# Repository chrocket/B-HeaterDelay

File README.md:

# B-HeaterDelay

B+ Heater Delay

SMD version of Pete Millett B++ heater delay (only delay portion) http://www.pmillett.com/mec\_power\_supply\_delay.html

The "main" branch has a one relay version.  Use 6/28/25 production files

Branch "dual" has two relays.  Use B_Delay_20260203_rev5d.zip production files.

I'm using KiCad 9.0.0

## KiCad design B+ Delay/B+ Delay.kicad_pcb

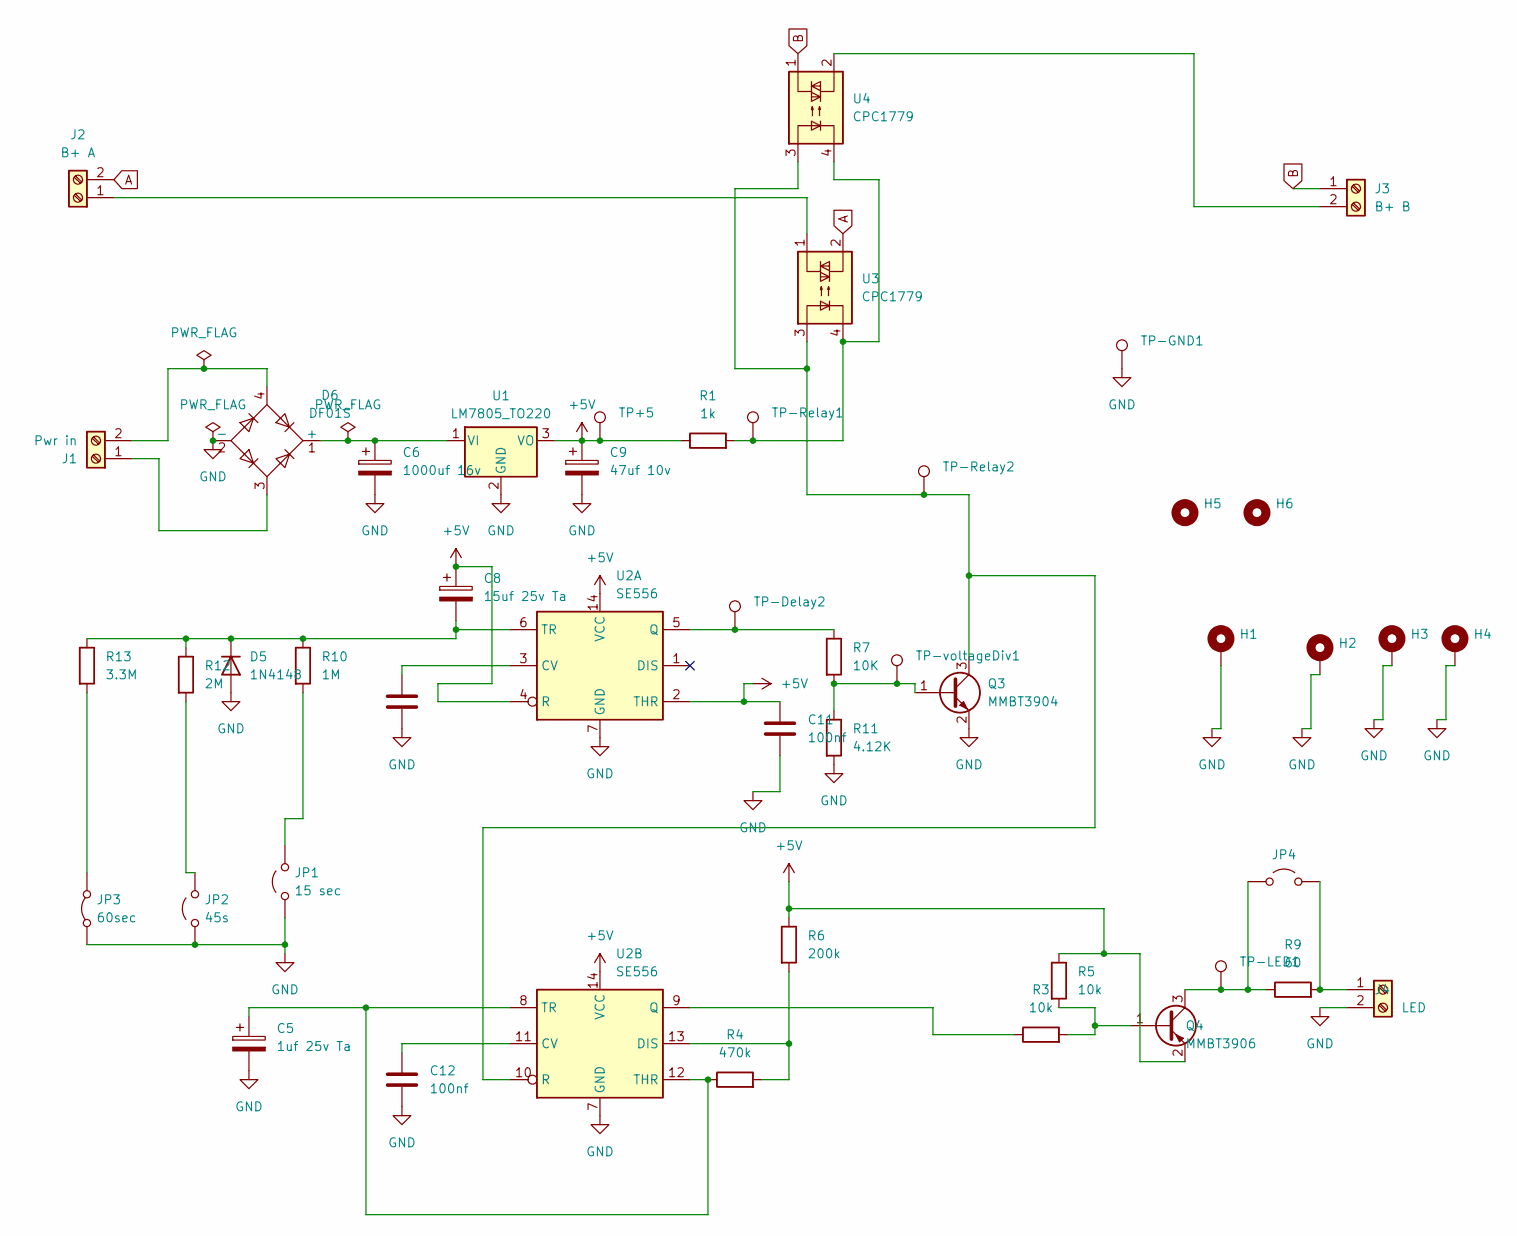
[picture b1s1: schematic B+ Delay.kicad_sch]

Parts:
C5: 1uf 25v Ta; C_0805_2012Metric_Pad1.18x1.45mm_HandSolder; Mouser 74-TMCP1E105KTRF
C6: 1000uf 16v; CP_Elec_10x7.7; Mouser 647-UCL1C102MNL1GS
C8: 15uf 25v Ta; C_1210_3225Metric_Pad1.33x2.70mm_HandSolder; Mouser 581-TPSB156K016R0800
C9: 47uf 10v; CP_Elec_10x7.7; Mouser 647-PCF1E470MCL1GS
C10, C11, C12: 100nf; C_0805_2012Metric; LCSC C49678
D5: 1N4148; D_SOD-123; LCSC C2128
D6: DF01S; Diode_Bridge_OnSemi_SDIP-4L; Mouser 621-DF01ST
H1, H2, H3, H4: MountingHole_4.3mm_M4_DIN965_Pad_TopBottom
H5: MountingHole; MountingHole_3.2mm_M3_Pad_TopBottom
H6: MountingHole; MountingHole_3.2mm_M3_ISO14580_Pad_TopBottom
J1: Pwr in; TerminalBlock_Phoenix_PT-1,5-2-3.5-H_1x02_P3.50mm_Horizontal
J2: B+ A; TerminalBlock_CUI_TB007-508-02_1x02_P5.08mm_Horizontal
J3: B+ B; TerminalBlock_CUI_TB007-508-02_1x02_P5.08mm_Horizontal
J4: LED; TerminalBlock_Phoenix_PT-1,5-2-3.5-H_1x02_P3.50mm_Horizontal
JP1: 15 sec; SolderJumper-2_P1.3mm_Open_RoundedPad1.0x1.5mm
JP2: 45s; SolderJumper-2_P1.3mm_Open_RoundedPad1.0x1.5mm
JP3: 60sec; SolderJumper-2_P1.3mm_Bridged_Pad1.0x1.5mm
JP4: Jumper_2_Open; SolderJumper-2_P1.3mm_Open_RoundedPad1.0x1.5mm
Q3: MMBT3904; SOT-23; LCSC C20526
Q4: MMBT3906; SOT-23; LCSC C5300004
R1: 1k; R_0805_2012Metric_Pad1.20x1.40mm_HandSolder; LCSC C17513
R3, R5: 10k; R_0805_2012Metric_Pad1.20x1.40mm_HandSolder; LCSC C17414
R4: 470k; R_0805_2012Metric_Pad1.20x1.40mm_HandSolder; LCSC C17709
R6: 200k; R_0805_2012Metric_Pad1.20x1.40mm_HandSolder; LCSC C17539
R7: 10K; R_0805_2012Metric_Pad1.20x1.40mm_HandSolder; LCSC C17414
R9: 60; R_0805_2012Metric_Pad1.20x1.40mm_HandSolder; LCSC C17757
R10: 1M; R_0805_2012Metric_Pad1.20x1.40mm_HandSolder; LCSC C17514
R11: 4.12K; R_0805_2012Metric_Pad1.20x1.40mm_HandSolder; LCSC C17667
R12: 2M; R_0805_2012Metric_Pad1.20x1.40mm_HandSolder; LCSC C17514
R13: 3.3M; R_0805_2012Metric_Pad1.20x1.40mm_HandSolder; LCSC C17514
TP+5: TestPoint_Keystone_5019_Miniature
TP-Delay2: TestPoint_Keystone_5019_Miniature
TP-GND1: TestPoint_Keystone_5019_Miniature
TP-LED1: TestPoint_Keystone_5019_Miniature
TP-Relay1, TP-Relay2: TestPoint_Keystone_5019_Miniature
TP-voltageDiv1: TestPoint_Keystone_5019_Miniature
U1: LM7805_TO220; TO-252-2; LCSC C110908
U2: SE556; SOIC-14_3.9x8.7mm_P1.27mm; LCSC C7427
U3, U4: CPC1779; CPC1779J

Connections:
+5V: C8.1, C9.1, C11.1, Q4.2 (E), R1.1, R5.1, R6.1, TP+5.1, U1.3 (VO), U2.2 (THR), U2.4 (R), U2.14 (VCC)
A: J2.2, U3.2
B: J3.1, U4.1
GND: C5.2, C6.2, C9.2, C10.2, C11.2, C12.2, D5.2 (A), D6.2 (-), H1.1, H2.1, H3.1, H4.1, J4.2, JP1.1 (A), JP2.1 (A), JP3.1 (A), Q3.2 (E), R11.2, TP-GND1.1, U1.2 (GND), U2.7 (GND)
unnamed: C8.2, D5.1 (K), R10.1, R12.1, R13.1, U2.6 (TR)
unnamed: C6.1, D6.1 (+), U1.1 (VI)
unnamed: D6.3, J1.1
unnamed: D6.4, J1.2
unnamed: J2.1, U3.1
unnamed: J3.2, U4.2
unnamed: J4.1, JP4.2 (B), R9.2
unnamed: JP1.2 (B), R10.2
unnamed: JP2.2 (B), R12.2
unnamed: JP3.2 (B), R13.2
unnamed: JP4.1 (A), Q4.3 (C), R9.1, TP-LED1.1
unnamed: Q3.1 (B), R7.2, R11.1, TP-voltageDiv1.1
unnamed: Q3.3 (C), TP-Relay2.1, U2.10 (R), U3.3, U4.3
unnamed: Q4.1 (B), R3.2, R5.2
unnamed: R1.2, TP-Relay1.1, U3.4, U4.4
unnamed: C10.1, U2.3 (CV)
unnamed: R7.1, TP-Delay2.1, U2.5 (Q)
unnamed: C12.1, U2.11 (CV)
unnamed: R4.2, R6.2, U2.13 (DIS)
unnamed: R3.1, U2.9 (Q)
unnamed: C5.1, R4.1, U2.8 (TR), U2.12 (THR)

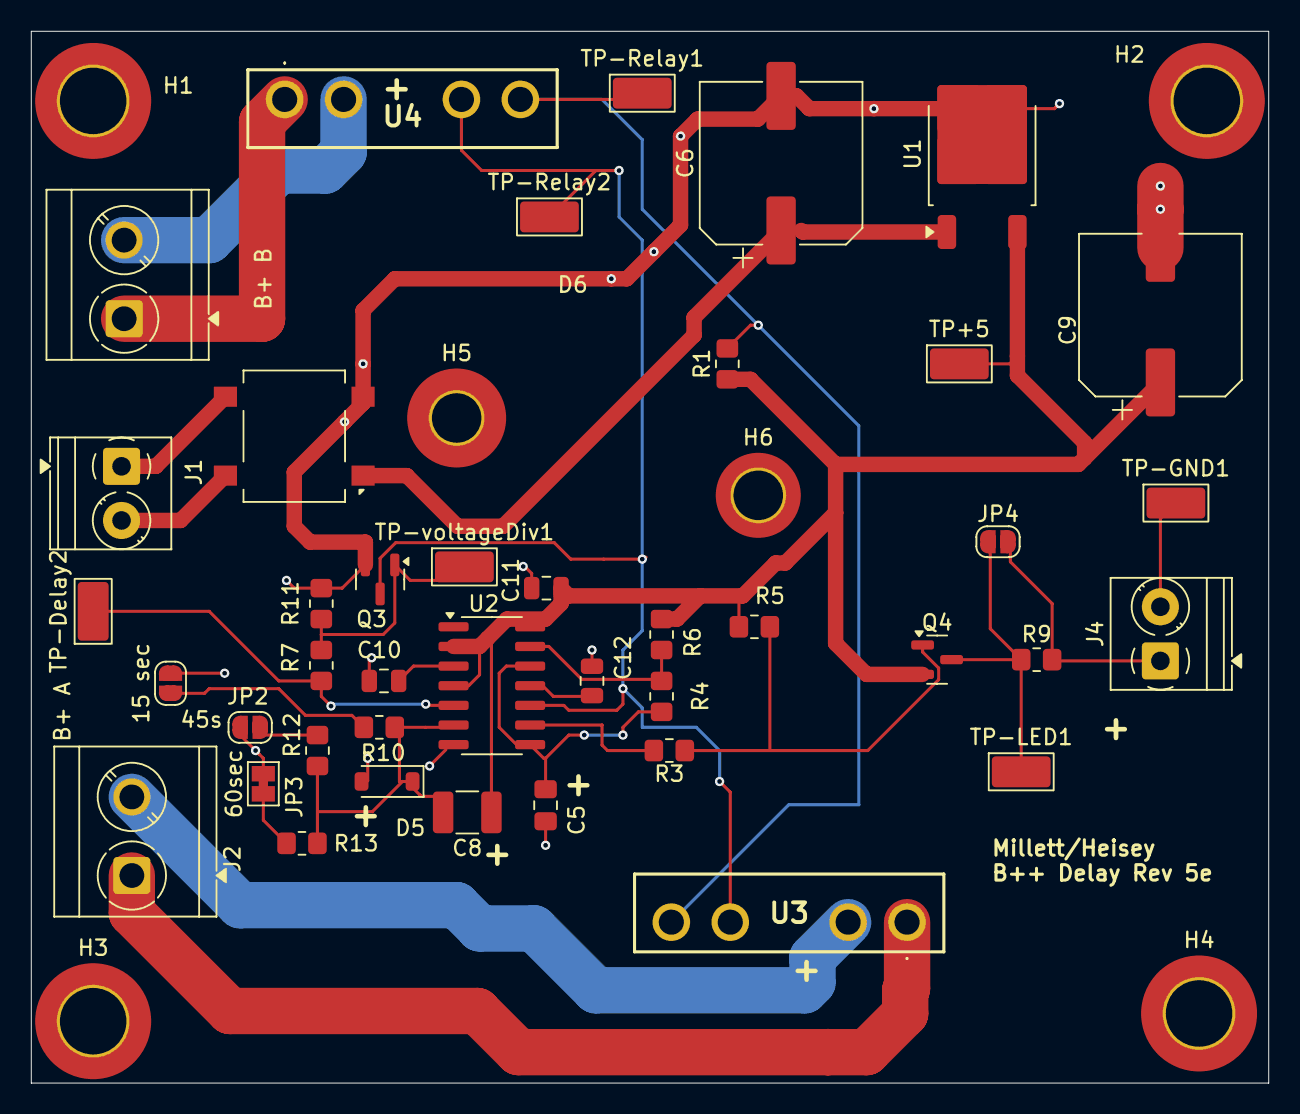
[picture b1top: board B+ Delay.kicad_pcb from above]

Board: 2 copper layers, 80.0 x 68.0 mm, 47 parts (0 on the bottom side), 25 nets.

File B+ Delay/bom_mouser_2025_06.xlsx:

Designator | Footprint | Quantity used | Quantity Order | Value | Mouser Part Number
C10, C11, C12 | 805 | 3 |  | 100nf | 0805B104K250CT
C5 | 805 | 1 |  | 1uf 25v Ta | TMCP1E105KTRF
C6 | CP_Elec_10x7.7 | 1 |  | 1000uf 16v | 667-EEE-FK1A102GP
C8 | 1210 | 1 |  | 15uf 25v Ta | TPSB156K016R0800
C9 | CP_Elec_10x7.7 | 1 |  | 47uf 10v | 667-EEE-FK1K470P
D5 | 805 | 1 |  | 1N4148 | 241-1N4148W_R1_00001
D6 | Diode_Bridge_OnSemi_SDIP-4L | 1 |  | DF01S | 621-DF01ST
J1,J4 | TerminalBlock_Phoenix_PT-1,5-2-3.5-H_1x02_P3.50mm_Horizontal | 2 |  | Pwr in | 845-29.002
J2,J3 | TerminalBlock_CUI_TB007-508-02_1x02_P5.08mm_Horizontal | 2 |  | B+ IN | 490-TB007-508-02BE
Q3 | SOT-23 | 1 |  | MMBT3904 | 637-MMBT3904
Q4 | SOT-23 | 1 |  | MMBT3906 | 637-MMBT3906
R1 | 805 | 1 |  | 1k | 652-CR0805AFX1001EAS
R10 | 805 | 1 |  | 1M | AR0805FR-071ML
R11 | 805 | 1 |  | 4.12K | 652-CR0805FX-4121ELF
R3, R5, R7 | 805 | 3 |  | 10k | 71-CRCW080510K0JNEB
R4 | 805 | 1 |  | 470k | 652-CR0805JW-474ELF
R6 | 805 | 1 |  | 200k | 652-CR0805FX-2003ELF
R9 | 805 | 1 |  | 60 | 652-CR0805FX-68R0ELF
U1 | TO-252-2 | 1 |  | LM7805_TO220 | 621-AS7805ADTR-G1
U2 | SOIC-14_3.9x8.7mm_P1.27mm | 1 |  | SE556 | 595-NE556DR
U3 | CPC1779J | 1 |  | CPC1779 | 849-CPC1779J

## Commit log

2025-12-24 Release w/single relay, and JLCPCB production files
2025-12-26 Clean-up of production files
2025-12-26 Production files
2025-12-26 Adding photo
2025-12-26 Adding schematic
2025-12-26 Adding dual realay schematic
2025-12-29 Updated resistors to correct 0805 case
2026-01-19 New rev, dual relay, fixed stuff
    Fixing missing ground trace, correct footprint for diode, added test points, changed B++ input/output on terminal block
2026-01-19 oops ignore last version
2026-01-20 Production batch
    Putting one relay on top, another on bottom
2026-02-01 Rev 5
    Moved power supply parts so they don't bump SS relays, if they are bent over. Put 2nd relay so foil side is up for heatsink
2026-02-02 Moving terminal block over
2026-02-02 Added 2 more time values w jumpers
    default to 15s
2026-02-03 Made 60s default
    Jumpers for 45s and 15s
2026-02-09 next rev
2026-02-25 Latest production build
2026-02-25 Add production build file information to README
    Specify the production build file for deployment.
2026-02-25 Update production file reference in README
